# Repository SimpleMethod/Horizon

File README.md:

# 📡Horizon - Meteorological System based on Internet of things

# 🥰 Best engineering thesis at university of technology in faculty of Electrical Engineering, Automatics and Computer Science 🥰
https://weaii.tu.kielce.pl/2020/05/15/wyniki-konkursu-prac-dyplomowych-ieee-2020/

# 🧗‍♂️Main milestones

1. Development of a device for measuring atmospheric conditions.
2. Development of a device for receiving telemetry and sending it to IoT server. 
3. Development of an IoT server able to collect data and analyse.
4. Development of an instrument for wind direction mapping.  

# 🚀 Features
 1. Getting meteorological data such as:
 - Air temperature,
 - Atmospheric pressure,
- Air humidity,
- Soil moisture,
- Wind direction,
- Dust value 2.5 PM and 10 PM.
2.  Communication between weather stations and base stations using IEEE 802.11 standard.
3.  Sending received data to IoT server via GSM communication from base stations.
4.  Ability to view data via a graphical interface from any device.
5. IoT server aggregating and analyzing data. 

# 🗺️ Technologies used in project 
1. Weather station:
- Based on two microcontainers:  STM32 and ESP32 programmed in C++. Development of necessary libraries based on technical documentation,
- Used LTC415 as voltage monitor,
- Photovoltaic panels,
- Voltage regulator,
- Gel rechargeable battery.
2. Receiving station:
- Used ESP32  programmed in C++. Development of necessary libraries based on technical documentation,
- Used SIM700e as GSM modem.
3. IoT server:
- Used microservice architecture,
- Based completely on AWS services (AWS Lambda, Amazon DynamoDB, API gateway, IAM), Lambda programmed in Node.JS,
- Graphical interface based on AngularJS running in one page. 

# 🧪 Visualization of weather station PCB 

## 🧶  Weather station communication diagram

# 📈  Communication diagram

# 🧊 Database schema

# 📙 Soil moisture sensor case

# 🧭 Wind vane 
Working on the measurement of change of resistance.

## Visualization of PCB

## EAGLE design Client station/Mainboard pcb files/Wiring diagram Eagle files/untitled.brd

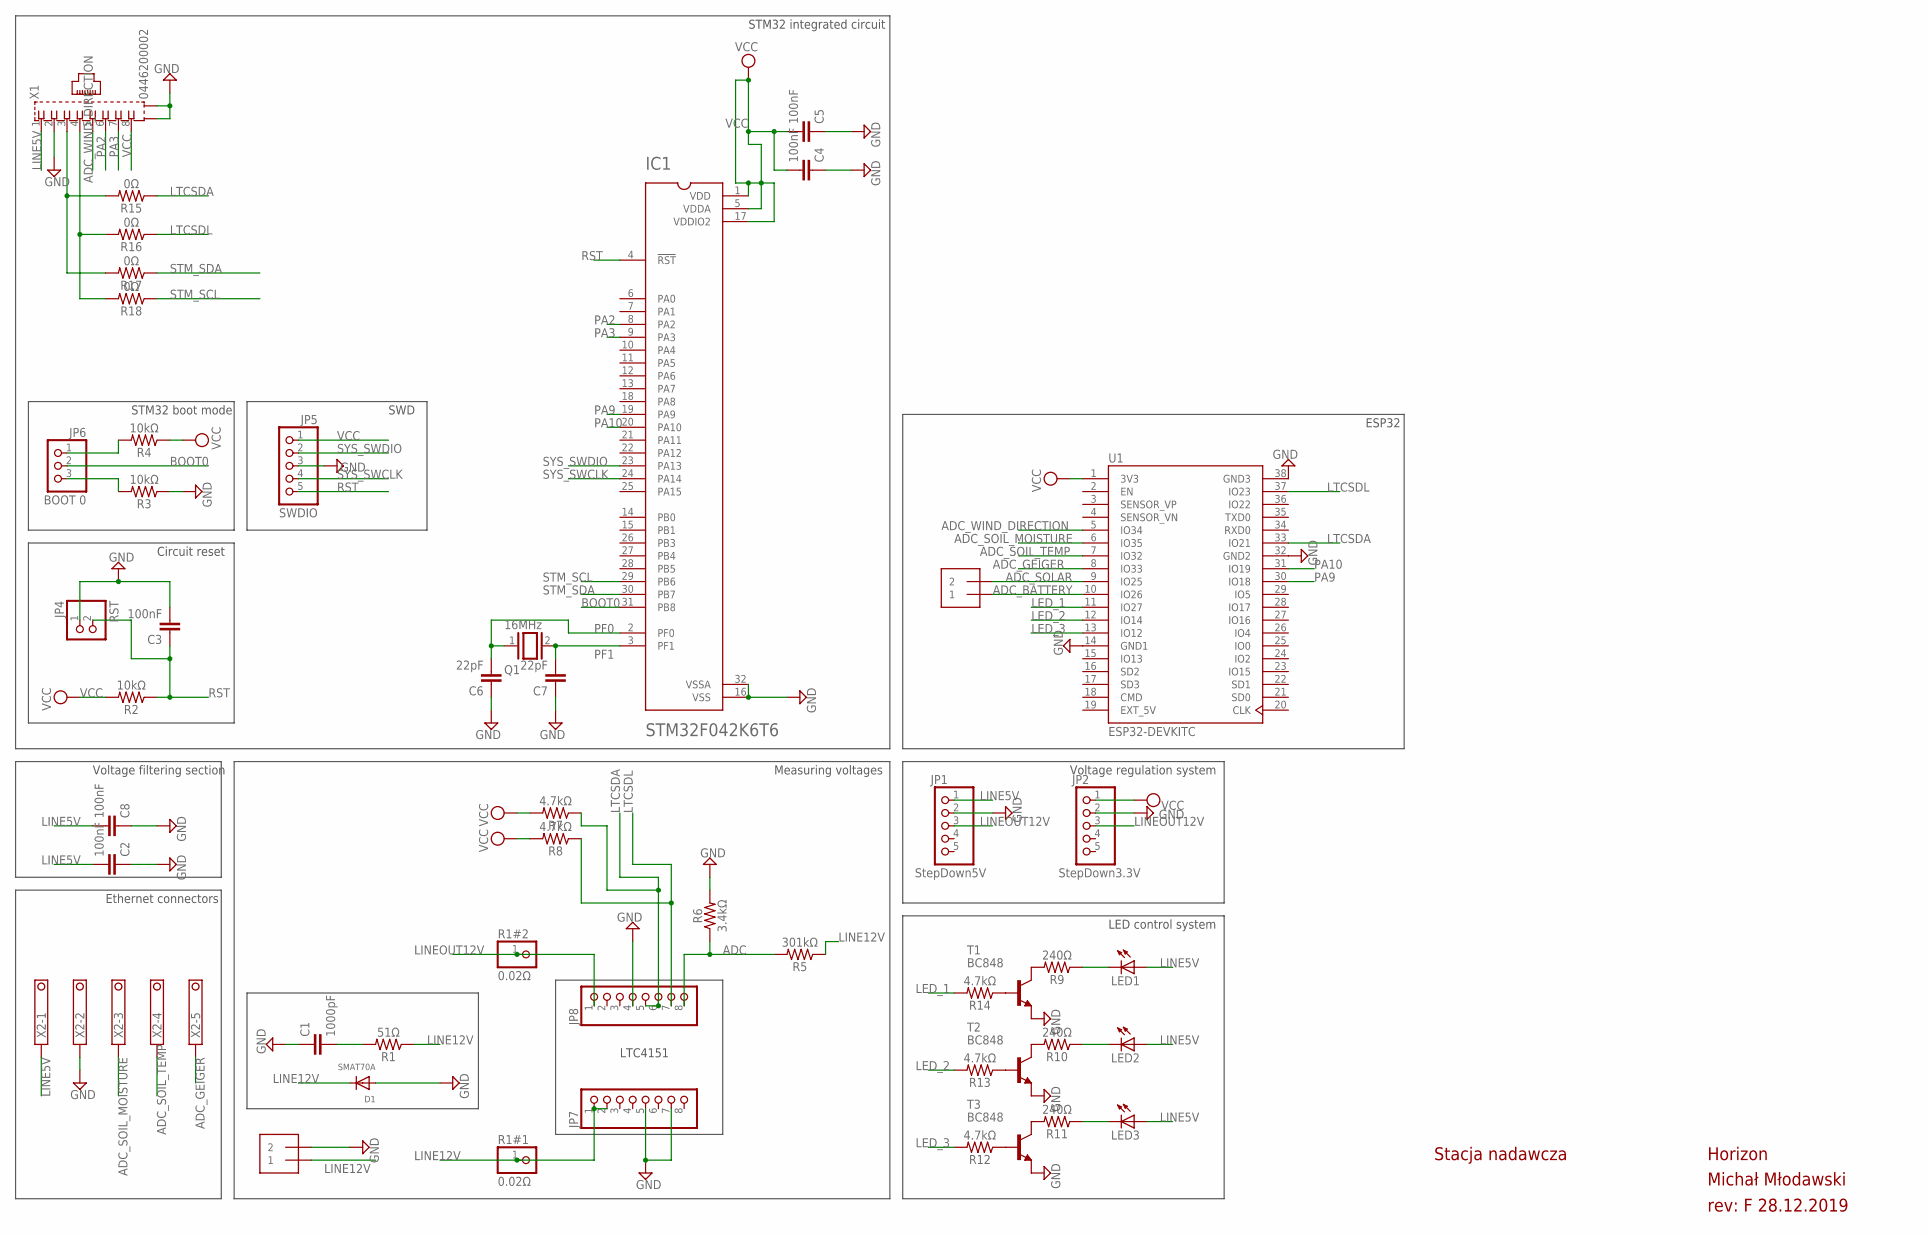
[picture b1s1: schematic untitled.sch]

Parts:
C1: 1000pF; 1206
C2, C3, C4, C5, C8: 100nF; 1206
C6, C7: 22pF; 1206
D1: SMAT70A; SMADIODE
IC1: STM32F042K6T6; QFP80P900X900X160-32N
J1, J2: 1X2-3.5MM
JP1: StepDown5V; 1X05
JP2: StepDown3.3V; 1X05
JP4: RST; 1X02
JP5: SWDIO; 1X05
JP6: BOOT 0; 1X03
JP7, JP8: PINHD-1X8; 1X08
LED1, LED2, LED3: LED5MM
Q1: 16MHz; QS
R1: 51Ω; 1206
R1#1, R1#2: 0.02Ω; 1X01
R2, R3, R4: 10kΩ; 1206
R5: 301kΩ; 1206
R6: 3.4kΩ; 1206
R7, R8, R12, R13, R14: 4.7kΩ; 1206
R9, R10, R11: 240Ω; 1206
R15, R16, R17, R18: 0Ω; 1206
T1, T2, T3: BC848; SOT23
U1: ESP32-DEVKITC; MODULE_ESP32-DEVKITC
X1: 0446200002
X2: TERMINAL-BLOCK-3.5MM-5-PIN-LONG-PAD; TERMINAL-BLOCK-5-PIN-3.5MM-LONG-PAD

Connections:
ADC: JP8.8, R5.2, R6.1
ADC_BATTERY: J1.1, U1.10 (IO26)
ADC_GEIGER: U1.8 (IO33), X2.5
ADC_SOIL_MOISTURE: U1.6 (IO35), X2.3
ADC_SOIL_TEMP: U1.7 (IO32), X2.4
ADC_SOLAR: J1.2, U1.9 (IO25)
ADC_WIND_DIRECTION: U1.5 (IO34), X1.5
BOOT0: IC1.31 (PB8), JP6.2
EXT_5V: U1.19 (EXT_5V)
GND: C1.1, C2.1, C3.2, C4.1, C5.1, C6.1, C7.1, C8.1, D1.A, IC1.16 (VSS), IC1.32 (VSSA), J2.2, JP1.2, JP2.2, JP4.1, JP5.3, JP7.5, JP7.7, JP8.4, R3.1, R6.2, T1.2 (E), T2.2 (E), T3.2 (E), U1.14 (GND1), U1.32 (GND2), U1.38 (GND3), X1.2, X1.S@1 (S1), X1.S@2 (S2), X2.2
LED_1: R14.2, U1.11 (IO27)
LED_2: R13.2, U1.12 (IO14)
LED_3: R12.2, U1.13 (IO12)
LINE5V: C2.2, C8.2, JP1.1, LED1.A, LED2.A, LED3.A, X1.1, X2.1
LINE12V: D1.C, J2.1, JP7.1, JP7.2, R1.1, R1#1.1, R5.1
LINEOUT12V: JP1.3, JP2.3, JP8.1, R1#2.1
LTCSDA: JP8.5, JP8.6, R7.1, R15.1, U1.33 (IO21)
LTCSDL: JP8.7, R8.1, R16.1, U1.37 (IO23)
unnamed: R9.2, T1.3 (C)
unnamed: R10.2, T2.3 (C)
unnamed: JP6.1, R4.2
unnamed: JP6.3, R3.2
unnamed: R11.2, T3.3 (C)
unnamed: C1.2, R1.2
unnamed: R12.1, T3.1 (B)
unnamed: R13.1, T2.1 (B)
unnamed: R14.1, T1.1 (B)
unnamed: LED3.K (C), R11.1
unnamed: LED2.K (C), R10.1
unnamed: LED1.K (C), R9.1
unnamed: R16.2, R18.2, X1.4
unnamed: R15.2, R17.2, X1.3
PA2: IC1.8 (PA2), X1.6
PA3: IC1.9 (PA3), X1.7
PA9: IC1.19 (PA9), U1.30 (IO18)
PA10: IC1.20 (PA10), U1.31 (IO19)
PF0: C6.2, IC1.2 (PF0), Q1.1
PF1: C7.2, IC1.3 (PF1), Q1.2
RST: C3.1, IC1.4 (!RST), JP4.2, JP5.5, R2.1
STM_SCL: IC1.29 (PB6), R18.1
STM_SDA: IC1.30 (PB7), R17.1
SYS_SWCLK: IC1.24 (PA14), JP5.4
SYS_SWDIO: IC1.23 (PA13), JP5.2
VCC: C4.2, C5.2, IC1.1 (VDD), IC1.5 (VDDA), IC1.17 (VDDIO2), JP2.1, JP5.1, R2.2, R4.1, R7.2, R8.2, U1.1 (3V3), X1.8

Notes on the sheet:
Circuit reset
SWD
Voltage regulation system
Ethernet connectors
STM32 boot mode
STM32 integrated circuit
Voltage filtering section
ESP32
LED control system
LTC4151
Measuring voltages
rev: F 28.12.2019
Michał Młodawski
Horizon
Stacja nadawcza

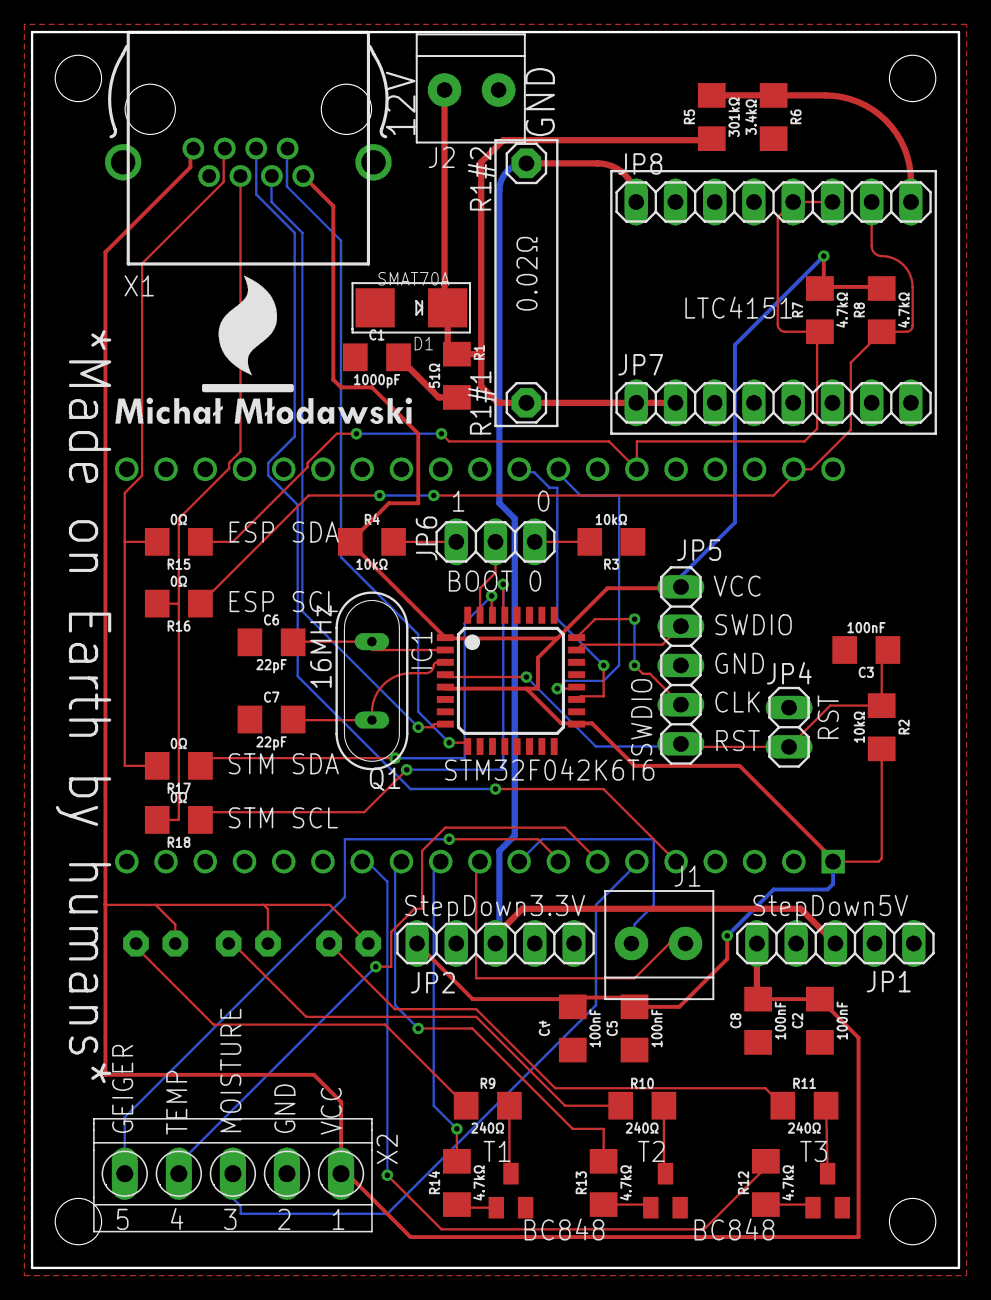
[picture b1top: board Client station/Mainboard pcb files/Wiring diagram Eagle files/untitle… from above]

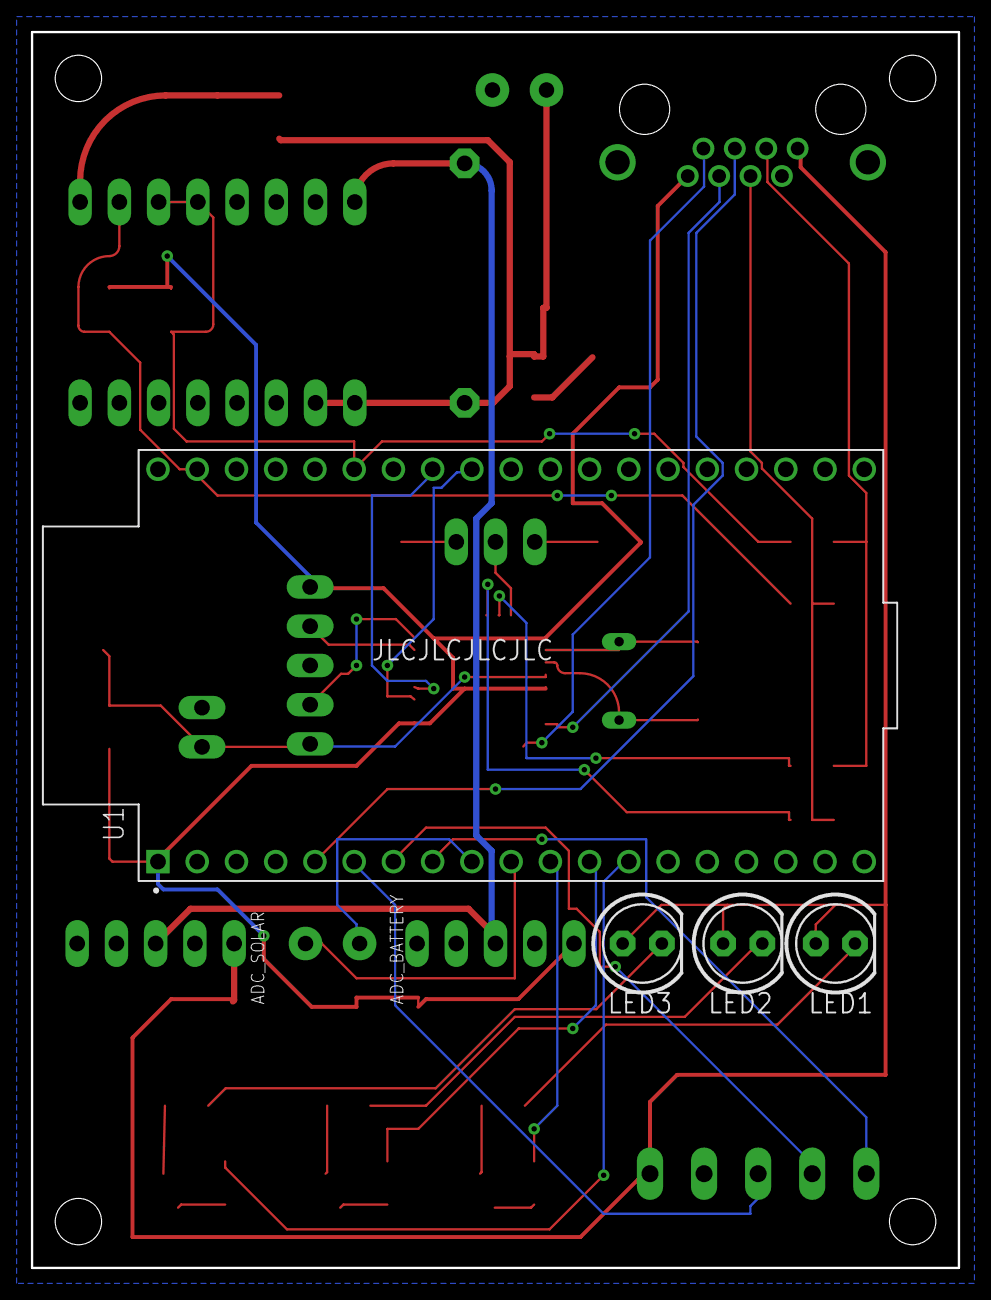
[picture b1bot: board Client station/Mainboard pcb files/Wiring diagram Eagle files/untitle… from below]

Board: 2 copper layers, 60.0 x 80.0 mm, 49 parts (4 on the bottom side), 43 nets.

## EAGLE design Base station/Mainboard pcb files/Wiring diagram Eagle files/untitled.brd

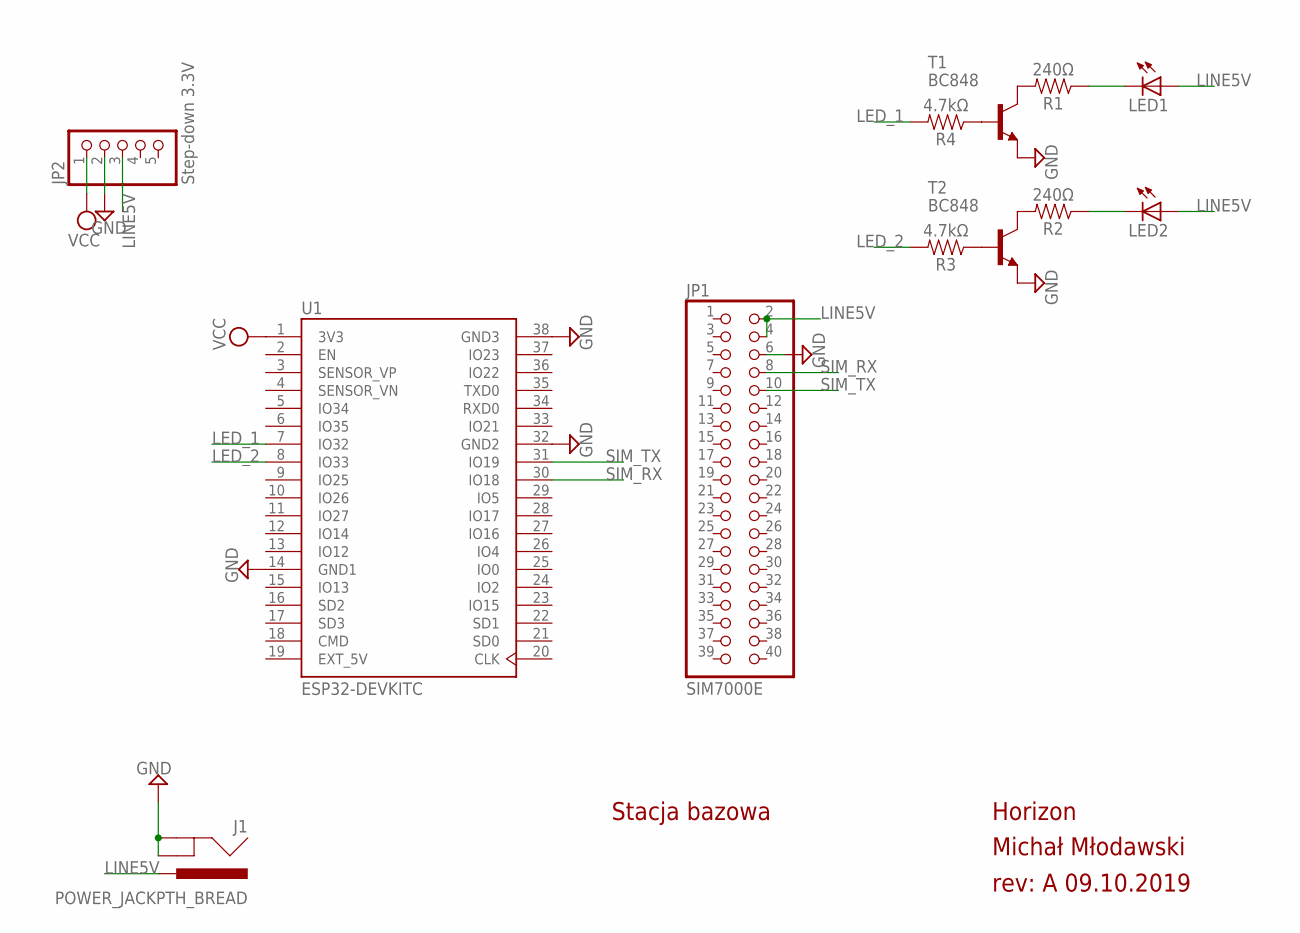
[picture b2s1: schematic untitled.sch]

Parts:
J1: POWER_JACKPTH_BREAD; POWER_JACK_PTH_BREAD
JP1: SIM7000E; 2X20
JP2: Step-down 3.3V; 1X05
LED1, LED2: LED5MM
R1, R2: 240Ω; 1206
R3, R4: 4.7kΩ; 1206
T1, T2: BC848; SOT23
U1: ESP32-DEVKITC; MODULE_ESP32-DEVKITC

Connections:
EXT_5V: U1.19 (EXT_5V)
GND: J1.GND, J1.GNDBREAK, JP1.6, JP2.2, T1.2 (E), T2.2 (E), U1.14 (GND1), U1.32 (GND2), U1.38 (GND3)
LED_1: R4.2, U1.7 (IO32)
LED_2: R3.2, U1.8 (IO33)
LINE5V: J1.PWR, JP1.2, JP1.4, JP2.3, LED1.A, LED2.A
unnamed: R1.2, T1.3 (C)
unnamed: R2.2, T2.3 (C)
unnamed: R3.1, T2.1 (B)
unnamed: R4.1, T1.1 (B)
unnamed: LED2.K (C), R2.1
unnamed: LED1.K (C), R1.1
SIM_RX: JP1.8, U1.30 (IO18)
SIM_TX: JP1.10, U1.31 (IO19)
VCC: JP2.1, U1.1 (3V3)

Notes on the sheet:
rev: A 09.10.2019
Michał Młodawski
Horizon
Stacja bazowa

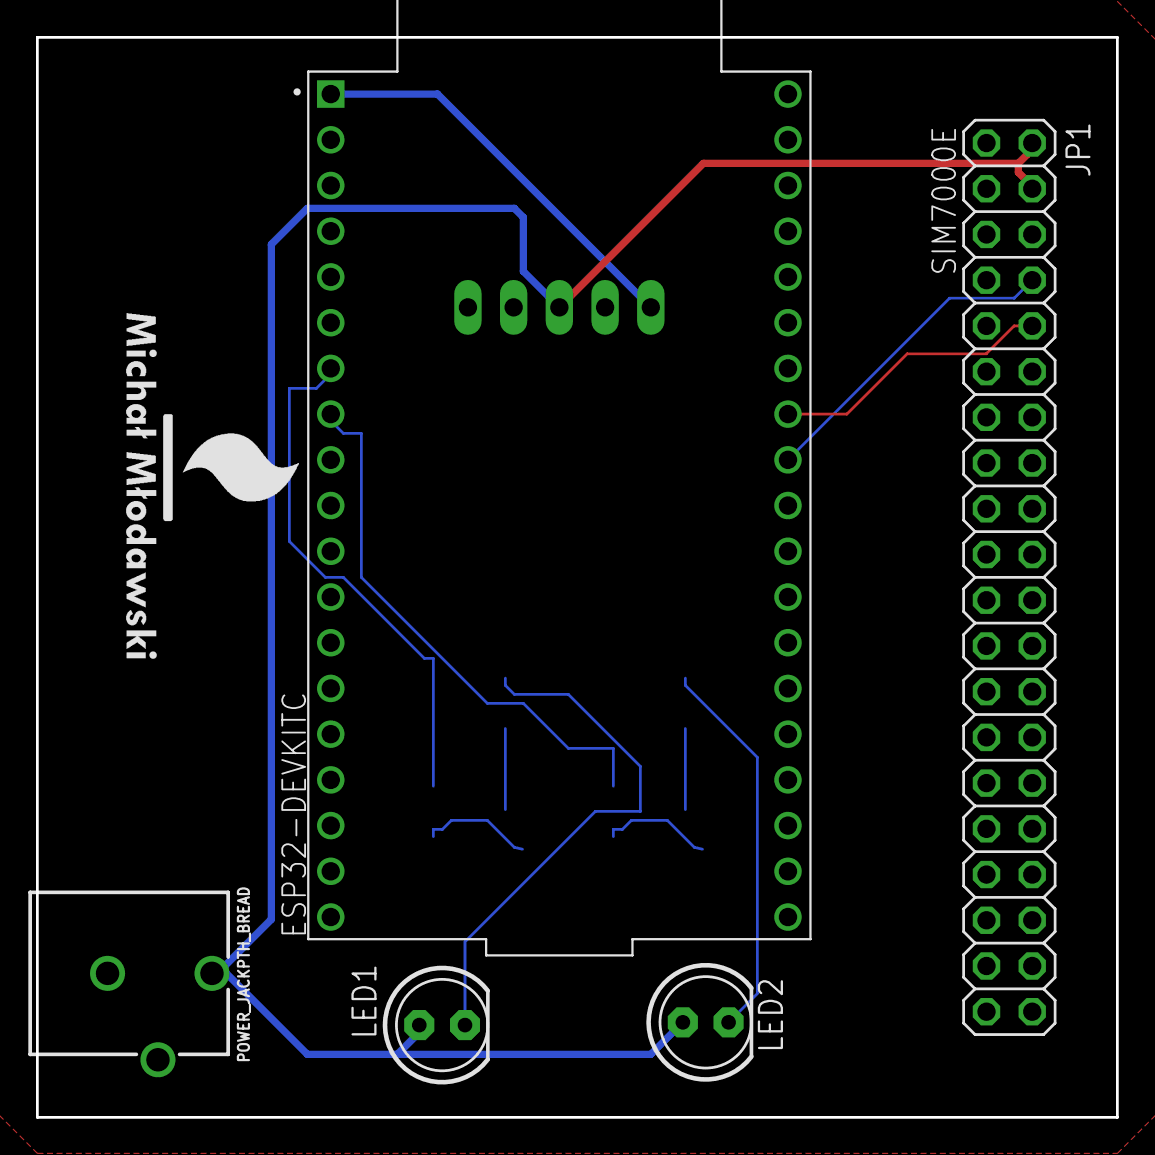
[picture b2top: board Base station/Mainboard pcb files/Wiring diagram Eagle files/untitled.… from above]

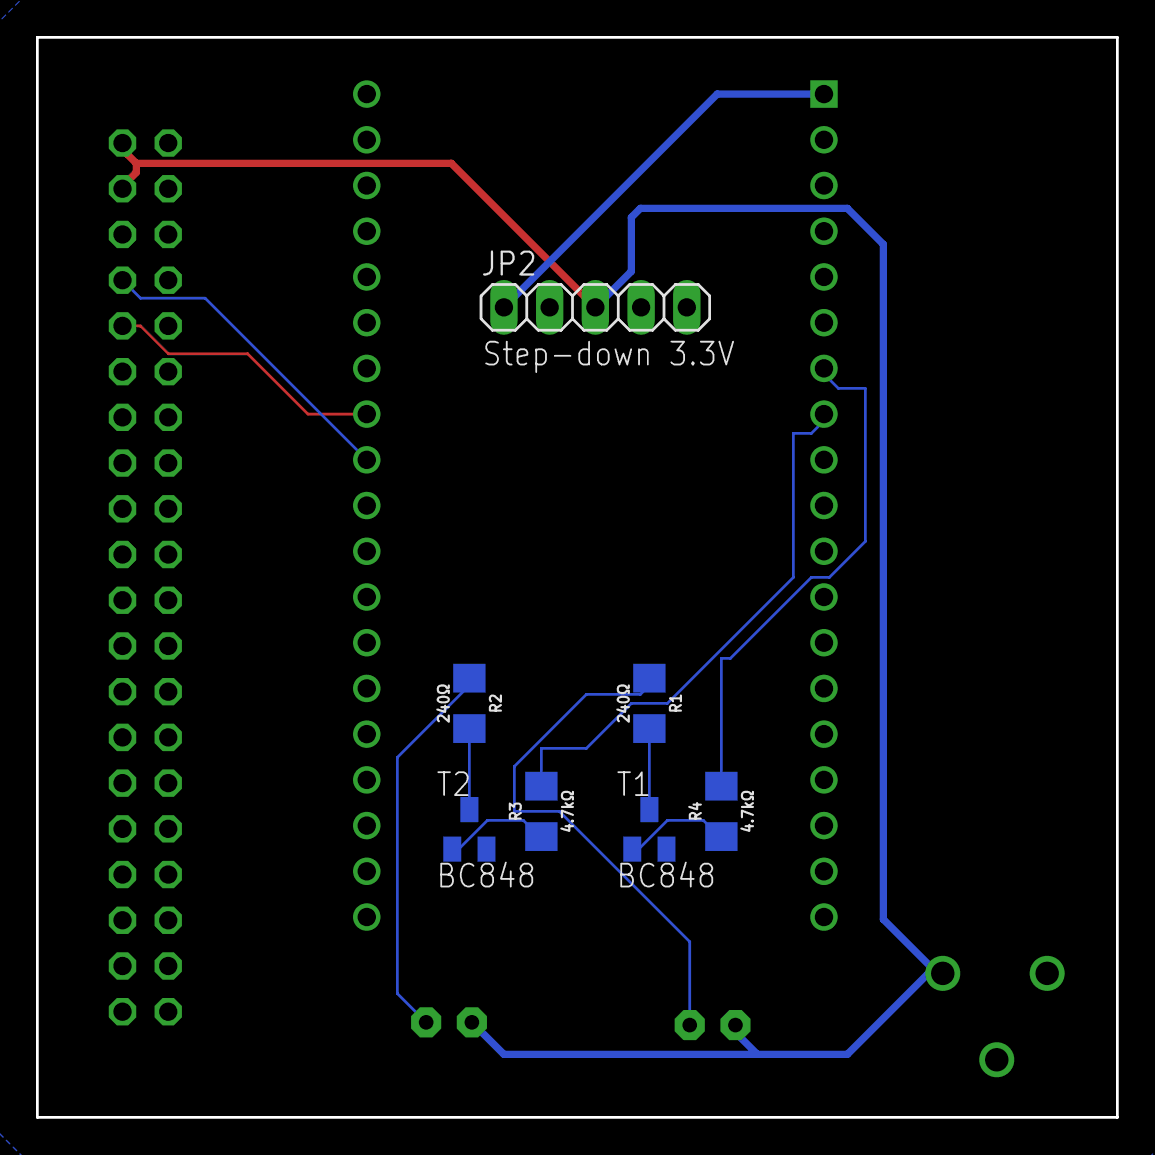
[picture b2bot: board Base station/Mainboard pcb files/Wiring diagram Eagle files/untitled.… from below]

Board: 2 copper layers, 60.0 x 60.0 mm, 12 parts (7 on the bottom side), 13 nets.

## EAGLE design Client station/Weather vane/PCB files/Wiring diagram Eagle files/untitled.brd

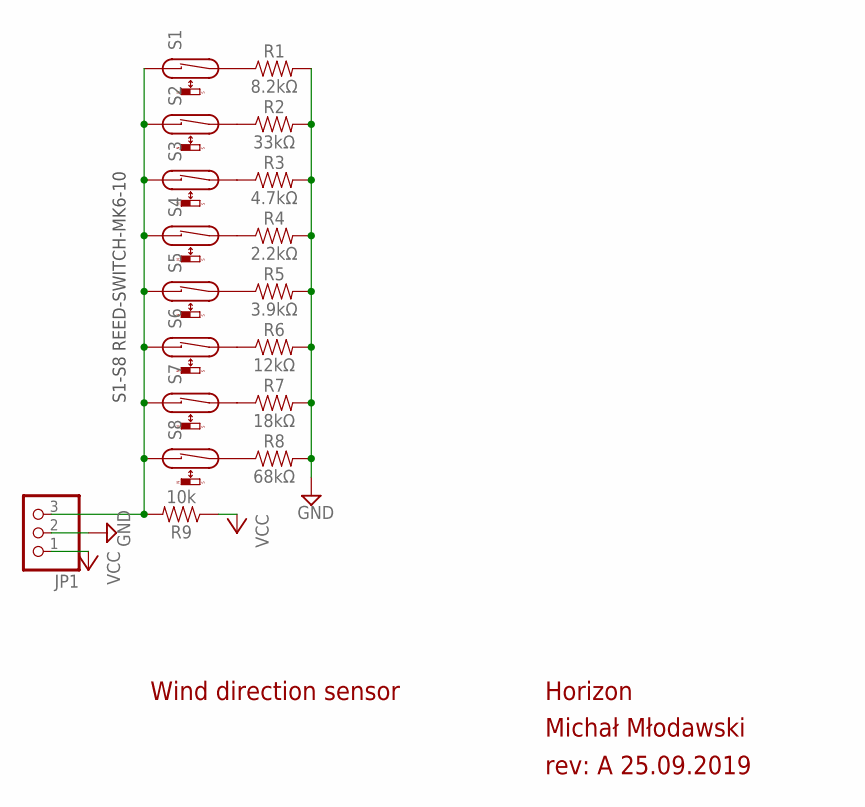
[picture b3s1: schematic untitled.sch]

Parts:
JP1: PINHD-1X3; 1X03
R1: 8.2kΩ; AXIAL-0.3
R2: 33kΩ; AXIAL-0.3
R3: 4.7kΩ; AXIAL-0.3
R4: 2.2kΩ; AXIAL-0.3
R5: 3.9kΩ; AXIAL-0.3
R6: 12kΩ; AXIAL-0.3
R7: 18kΩ; AXIAL-0.3
R8: 68kΩ; AXIAL-0.3
R9: 10k; AXIAL-0.3
S1, S2, S3, S4, S5, S6, S7, S8: REED-SWITCH-MK6-10; MK6-10

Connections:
GND: JP1.2, R1.P$2 (2), R2.P$2 (2), R3.P$2 (2), R4.P$2 (2), R5.P$2 (2), R6.P$2 (2), R7.P$2 (2), R8.P$2 (2)
unnamed: R1.P$1 (1), S1.2
unnamed: R2.P$1 (1), S2.2
unnamed: R3.P$1 (1), S3.2
unnamed: R4.P$1 (1), S4.2
unnamed: R5.P$1 (1), S5.2
unnamed: R6.P$1 (1), S6.2
unnamed: R7.P$1 (1), S7.2
unnamed: R8.P$1 (1), S8.2
unnamed: JP1.3, R9.P$2 (2), S1.1, S2.1, S3.1, S4.1, S5.1, S6.1, S7.1, S8.1
VCC: JP1.1, R9.P$1 (1)

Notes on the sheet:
S1-S8 REED-SWITCH-MK6-10
rev: A 25.09.2019
Michał Młodawski
Horizon
Wind direction sensor

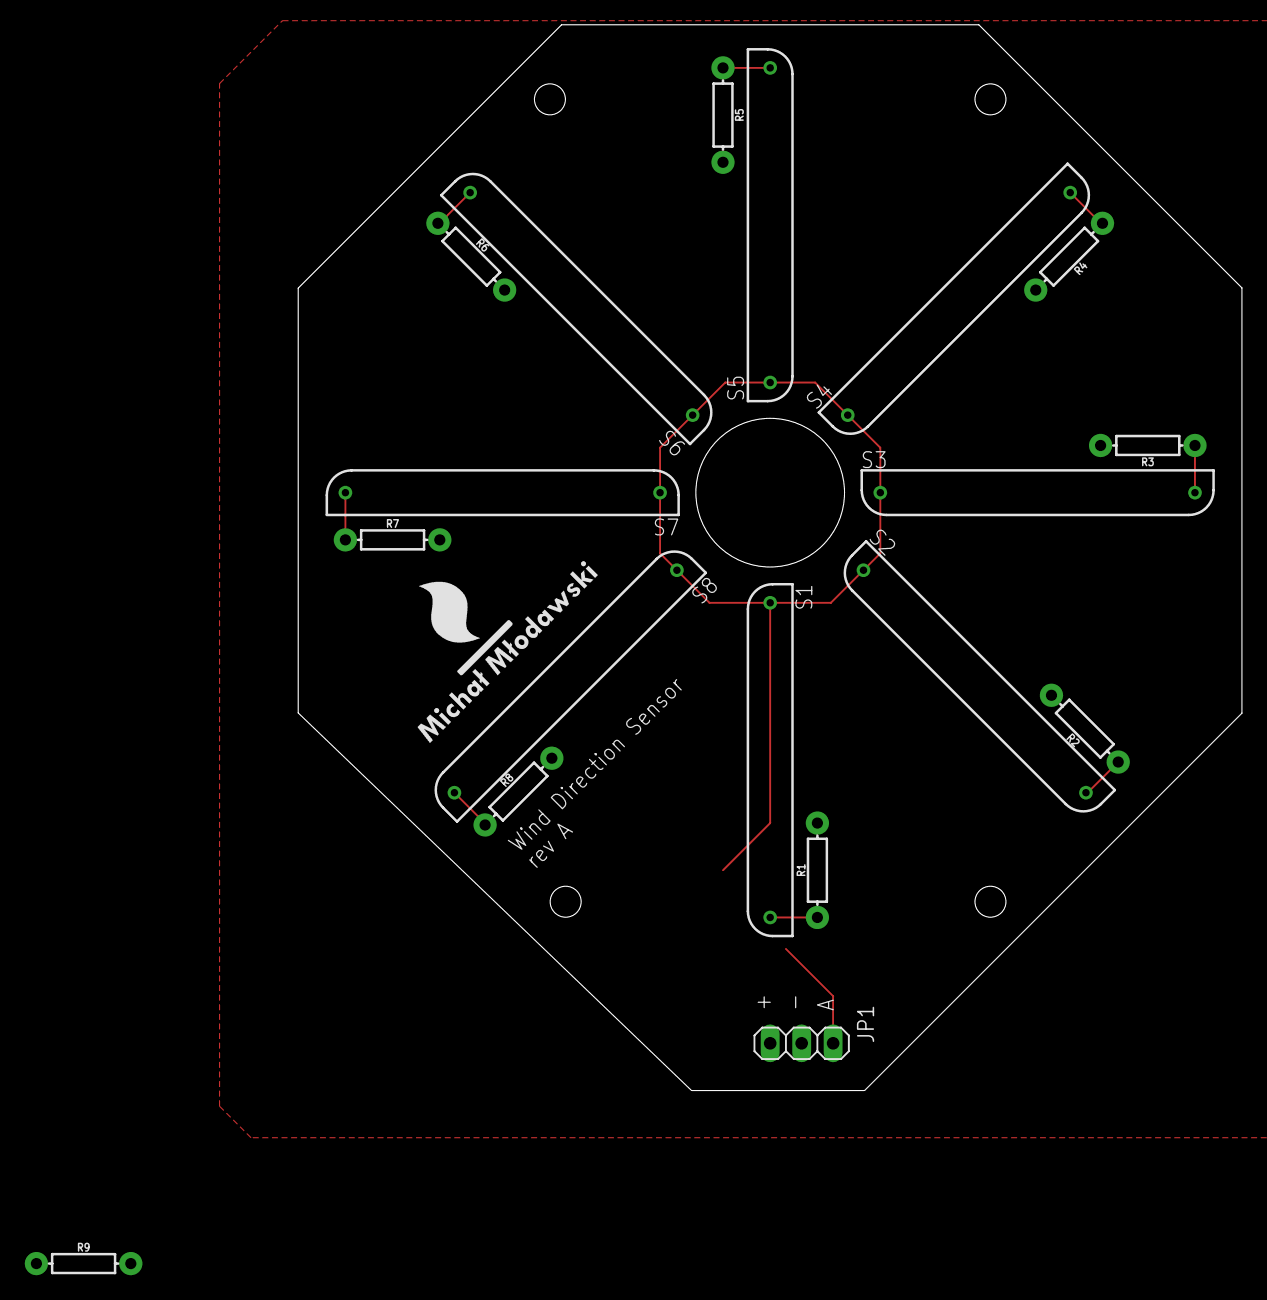
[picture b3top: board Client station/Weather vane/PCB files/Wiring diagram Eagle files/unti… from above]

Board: 2 copper layers, 76.2 x 86.0 mm, 18 parts (0 on the bottom side), 11 nets.

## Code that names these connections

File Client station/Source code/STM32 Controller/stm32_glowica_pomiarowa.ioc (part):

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Mcu.Name=STM32F042K(4-6)Tx
Mcu.Package=LQFP32
Mcu.UserName=STM32F042K6Tx
PA1.GPIOParameters=GPIO_Label
PA1.GPIO_Label=ADC_SOIL_MISTURE
PA1.Signal=ADC_IN1
PA10.GPIOParameters=GPIO_Label
PA10.GPIO_Label=UART1_ESP_RX
PA10.Mode=Asynchronous
PA10.Signal=USART1_RX
PA13.Mode=Serial_Wire
PA13.Signal=SYS_SWDIO
PA14.Mode=Serial_Wire
PA14.Signal=SYS_SWCLK
PA2.GPIOParameters=GPIO_Label
PA2.GPIO_Label=UART2_SDS011_TX
PA2.Mode=Asynchronous
PA2.Signal=USART2_TX
PA3.GPIOParameters=GPIO_Label
PA3.GPIO_Label=UART2_SDS011_RX
PA3.Mode=Asynchronous
PA3.Signal=USART2_RX
PA4.GPIOParameters=GPIO_Label
PA4.GPIO_Label=ADC_WIND_DIRECTION
PA4.Mode=IN4
PA4.Signal=ADC_IN4
PA9.GPIOParameters=GPIO_Label
PA9.GPIO_Label=UART1_ESP_TX
PA9.Mode=Asynchronous
PA9.Signal=USART1_TX
PB6.GPIOParameters=GPIO_Label
PB6.GPIO_Label=I2CL_BME_SCL
PB6.Mode=I2C
PB6.Signal=I2C1_SCL
PB7.GPIOParameters=GPIO_Label
PB7.GPIO_Label=I2C1_BME_SDA
PB7.Mode=I2C
PB7.Signal=I2C1_SDA
PF0-OSC_IN.Mode=HSE-External-Oscillator
PF0-OSC_IN.Signal=RCC_OSC_IN
PF1-OSC_OUT.Mode=HSE-External-Oscillator
PF1-OSC_OUT.Signal=RCC_OSC_OUT
RCC.HSE_VALUE=16000000
RCC.SYSCLKFreq_VALUE=48000000
RCC.SYSCLKSource=RCC_SYSCLKSOURCE_HSI48
board=custom

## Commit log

2020-05-23 Main files
2020-05-23 Update LICENSE

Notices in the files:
parts and their libraries:
SparkFun-Connectors: Licensing: Creative Commons ShareAlike 4.0 International - https://creativecommons.org/licenses/by-sa/4.0
